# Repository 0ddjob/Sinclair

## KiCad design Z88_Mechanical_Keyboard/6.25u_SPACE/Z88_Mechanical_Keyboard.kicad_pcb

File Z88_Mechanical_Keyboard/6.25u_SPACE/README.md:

# 6.25u SPACE BAR
This PCB design has the 6.25u SPACE and 1.75u CAPS LOCK.

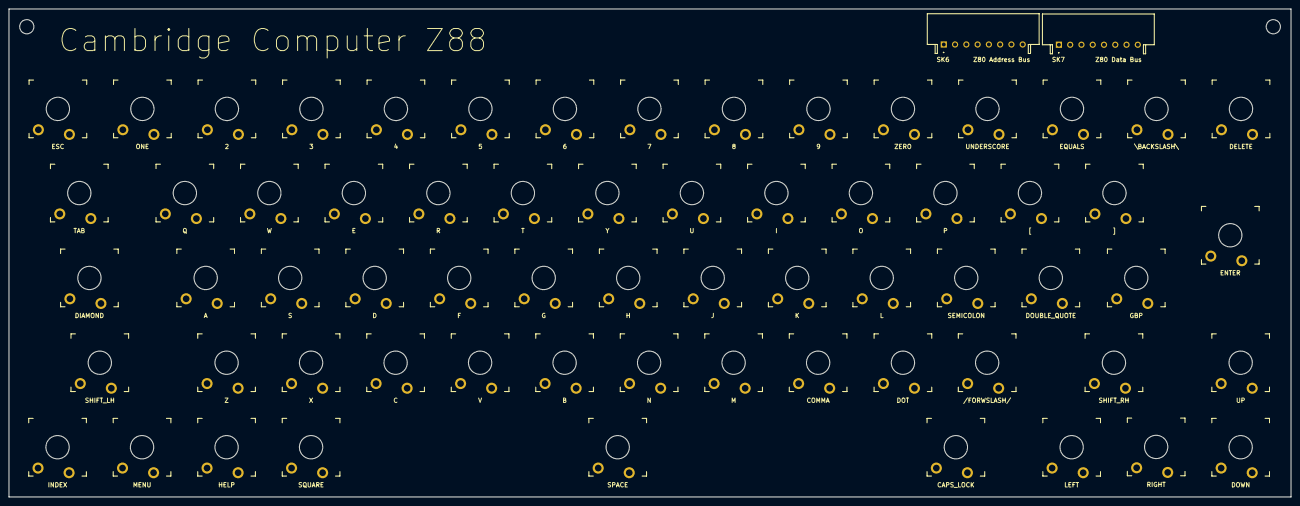
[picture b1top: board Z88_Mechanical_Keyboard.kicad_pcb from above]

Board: 2 copper layers, 289.0 x 110.0 mm, 68 parts (0 on the bottom side), 16 nets, no tracks yet.

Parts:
H1, H2: MountingHole; MountingHole_3.2mm_M3
SK6: Z80 Address Bus; 55203148
SK7: Z80 Data Bus; 55203148
SW1: SHIFT_RH; SW_Gateron_LowProfile_THT
SW2: HELP; SW_Gateron_LowProfile_THT
SW3: [; SW_Gateron_LowProfile_THT
SW4: ]; SW_Gateron_LowProfile_THT
SW5: UNDERSCORE; SW_Gateron_LowProfile_THT
SW6: EQUALS; SW_Gateron_LowProfile_THT
SW7: \BACKSLASH\; SW_Gateron_LowProfile_THT
SW8: DELETE; SW_Gateron_LowProfile_THT
SW9: SQUARE; SW_Gateron_LowProfile_THT
SW10: SHIFT_LH; SW_Gateron_LowProfile_THT
SW11: SPACE; SW_Gateron_LowProfile_THT
SW12: LEFT; SW_Gateron_LowProfile_THT
SW13: RIGHT; SW_Gateron_LowProfile_THT
SW14: DOWN; SW_Gateron_LowProfile_THT
SW15: UP; SW_Gateron_LowProfile_THT
SW16: ENTER; SW_Gateron_LowProfile_THT
SW17: ESC; SW_Gateron_LowProfile_THT
SW18: TAB; SW_Gateron_LowProfile_THT
SW19: ONE; SW_Gateron_LowProfile_THT
SW20: 2; SW_Gateron_LowProfile_THT
SW21: 3; SW_Gateron_LowProfile_THT
SW22: 4; SW_Gateron_LowProfile_THT
SW23: 5; SW_Gateron_LowProfile_THT
SW24: 6; SW_Gateron_LowProfile_THT
SW25: INDEX; SW_Gateron_LowProfile_THT
SW26: DIAMOND; SW_Gateron_LowProfile_THT
SW27: Q; SW_Gateron_LowProfile_THT
SW28: W; SW_Gateron_LowProfile_THT
SW29: E; SW_Gateron_LowProfile_THT
SW30: R; SW_Gateron_LowProfile_THT
SW31: T; SW_Gateron_LowProfile_THT
SW32: Y; SW_Gateron_LowProfile_THT
SW33: CAPS_LOCK; SW_Gateron_LowProfile_THT
SW34: MENU; SW_Gateron_LowProfile_THT
SW35: A; SW_Gateron_LowProfile_THT
SW36: S; SW_Gateron_LowProfile_THT
SW37: D; SW_Gateron_LowProfile_THT
SW38: F; SW_Gateron_LowProfile_THT
SW39: G; SW_Gateron_LowProfile_THT
SW40: H; SW_Gateron_LowProfile_THT
SW41: DOT; SW_Gateron_LowProfile_THT
SW42: COMMA; SW_Gateron_LowProfile_THT
SW43: Z; SW_Gateron_LowProfile_THT
SW44: X; SW_Gateron_LowProfile_THT
SW45: C; SW_Gateron_LowProfile_THT
SW46: V; SW_Gateron_LowProfile_THT
SW47: B; SW_Gateron_LowProfile_THT
SW48: N; SW_Gateron_LowProfile_THT
SW49: /FORWSLASH/; SW_Gateron_LowProfile_THT
SW50: SEMICOLON; SW_Gateron_LowProfile_THT
SW51: L; SW_Gateron_LowProfile_THT
SW52: M; SW_Gateron_LowProfile_THT
SW53: K; SW_Gateron_LowProfile_THT
SW54: J; SW_Gateron_LowProfile_THT
SW55: U; SW_Gateron_LowProfile_THT
SW56: 7; SW_Gateron_LowProfile_THT
SW57: GBP; SW_Gateron_LowProfile_THT
SW58: DOUBLE_QUOTE; SW_Gateron_LowProfile_THT
SW59: ZERO; SW_Gateron_LowProfile_THT
SW60: P; SW_Gateron_LowProfile_THT
SW61: 9; SW_Gateron_LowProfile_THT
SW62: O; SW_Gateron_LowProfile_THT
SW63: I; SW_Gateron_LowProfile_THT
SW64: 8; SW_Gateron_LowProfile_THT

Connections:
COL0: SK6.2, SW1.1, SW9.1, SW17.1, SW25.1, SW33.1, SW41.1, SW49.1, SW57.1
COL1: SK6.1, SW2.1, SW10.1, SW18.1, SW26.1, SW34.1, SW42.1, SW50.1, SW58.1
COL2: SK6.3, SW3.1, SW11.1, SW19.1, SW27.1, SW35.1, SW43.1, SW51.1, SW59.1
COL3: SK6.4, SW4.1, SW12.1, SW20.1, SW28.1, SW36.1, SW44.1, SW52.1, SW60.1
COL4: SK6.5, SW5.1, SW13.1, SW21.1, SW29.1, SW37.1, SW45.1, SW53.1, SW61.1
COL5: SK6.6, SW6.1, SW14.1, SW22.1, SW30.1, SW38.1, SW46.1, SW54.1, SW62.1
COL6: SK6.7, SW7.1, SW15.1, SW23.1, SW31.1, SW39.1, SW47.1, SW55.1, SW63.1
COL7: SK6.8, SW8.1, SW16.1, SW24.1, SW32.1, SW40.1, SW48.1, SW56.1, SW64.1
ROW0: SK7.5, SW1.2, SW2.2, SW3.2, SW4.2, SW5.2, SW6.2, SW7.2, SW8.2
ROW1: SK7.7, SW9.2, SW10.2, SW11.2, SW12.2, SW13.2, SW14.2, SW15.2, SW16.2
ROW2: SK7.1, SW17.2, SW18.2, SW19.2, SW20.2, SW21.2, SW22.2, SW23.2, SW24.2
ROW3: SK7.2, SW25.2, SW26.2, SW27.2, SW28.2, SW29.2, SW30.2, SW31.2, SW32.2
ROW4: SK7.3, SW33.2, SW34.2, SW35.2, SW36.2, SW37.2, SW38.2, SW39.2, SW40.2
ROW5: SK7.8, SW41.2, SW42.2, SW43.2, SW44.2, SW45.2, SW46.2, SW47.2, SW48.2
ROW6: SK7.4, SW49.2, SW50.2, SW51.2, SW52.2, SW53.2, SW54.2, SW55.2, SW56.2
ROW7: SK7.6, SW57.2, SW58.2, SW59.2, SW60.2, SW61.2, SW62.2, SW63.2, SW64.2

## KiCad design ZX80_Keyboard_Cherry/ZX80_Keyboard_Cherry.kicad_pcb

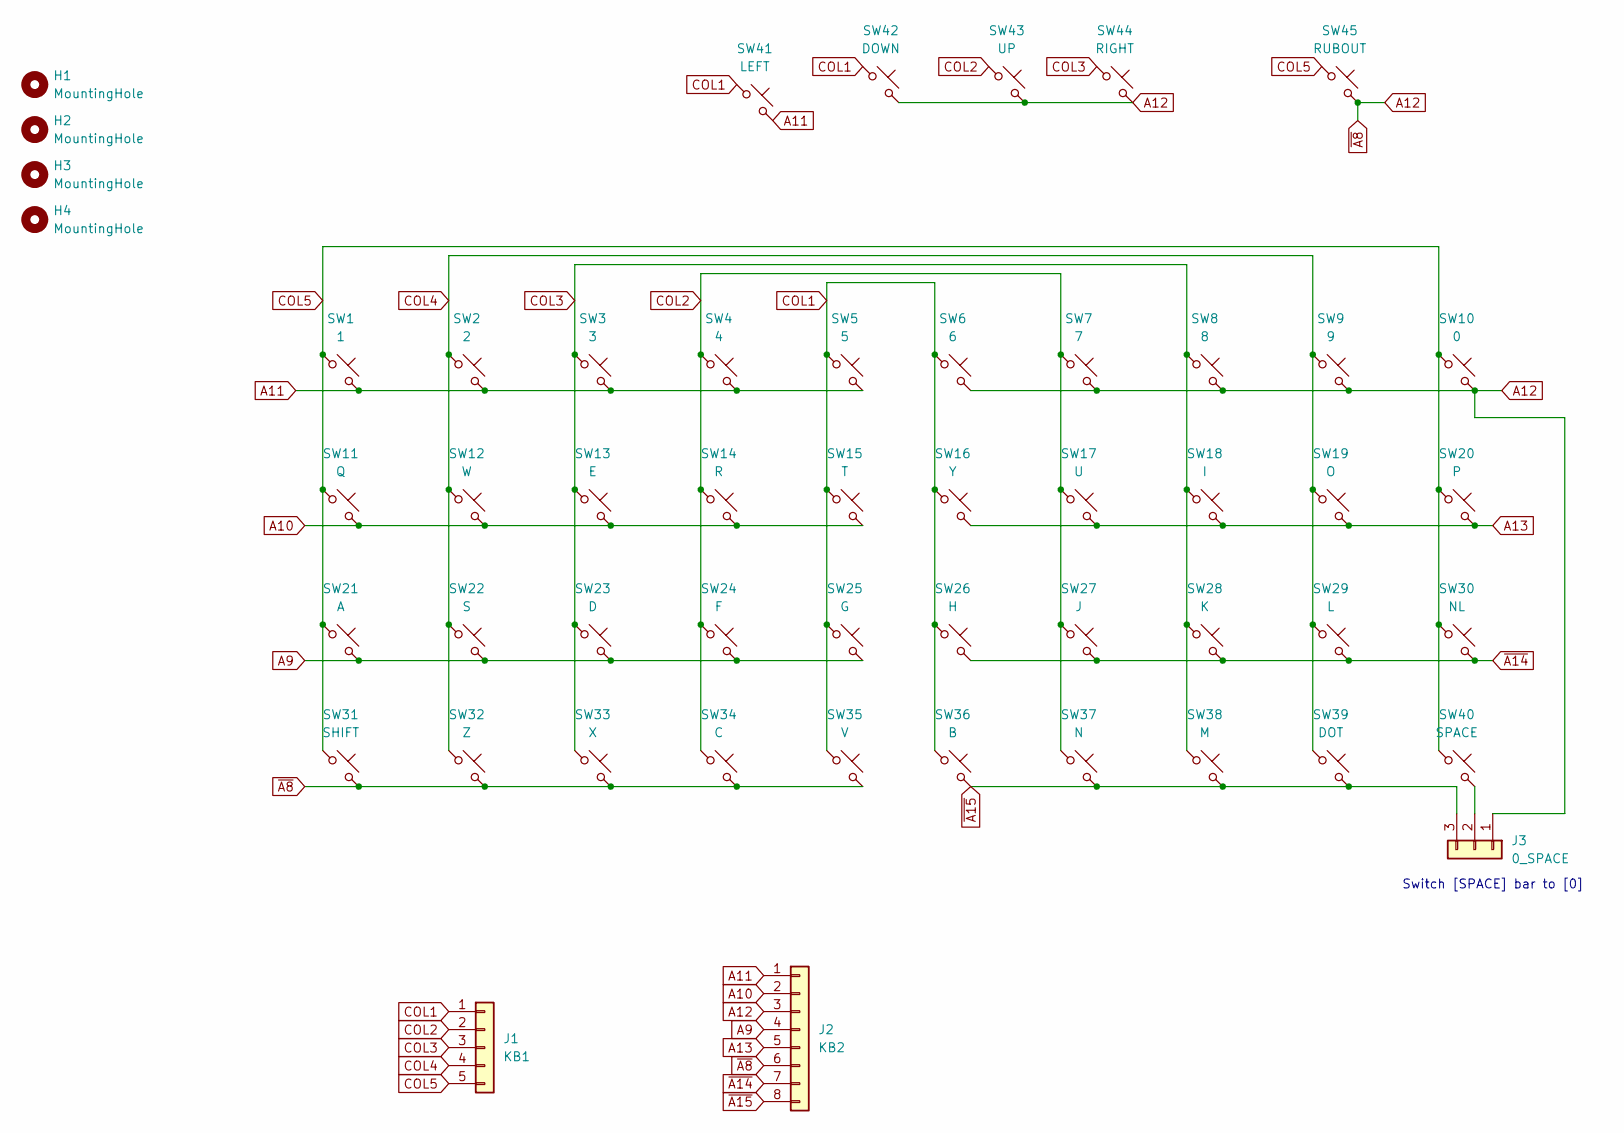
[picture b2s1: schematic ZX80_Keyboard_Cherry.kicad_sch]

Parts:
H1, H2, H3, H4: MountingHole; MountingHole_3.2mm_M3
J1: KB1; PinHeader_1x05_P2.54mm_Vertical
J2: KB2; PinHeader_1x08_P2.54mm_Vertical
J3: 0_SPACE; PinHeader_1x03_P2.54mm_Vertical
SW1: 1; SW_Cherry_MX_1.00u_PCB
SW2: 2; SW_Cherry_MX_1.00u_PCB
SW3: 3; SW_Cherry_MX_1.00u_PCB
SW4: 4; SW_Cherry_MX_1.00u_PCB
SW5: 5; SW_Cherry_MX_1.00u_PCB
SW6: 6; SW_Cherry_MX_1.00u_PCB
SW7: 7; SW_Cherry_MX_1.00u_PCB
SW8: 8; SW_Cherry_MX_1.00u_PCB
SW9: 9; SW_Cherry_MX_1.00u_PCB
SW10: 0; SW_Cherry_MX_1.00u_PCB
SW11: Q; SW_Cherry_MX_1.00u_PCB
SW12: W; SW_Cherry_MX_1.00u_PCB
SW13: E; SW_Cherry_MX_1.00u_PCB
SW14: R; SW_Cherry_MX_1.00u_PCB
SW15: T; SW_Cherry_MX_1.00u_PCB
SW16: Y; SW_Cherry_MX_1.00u_PCB
SW17: U; SW_Cherry_MX_1.00u_PCB
SW18: I; SW_Cherry_MX_1.00u_PCB
SW19: O; SW_Cherry_MX_1.00u_PCB
SW20: P; SW_Cherry_MX_1.00u_PCB
SW21: A; SW_Cherry_MX_1.00u_PCB
SW22: S; SW_Cherry_MX_1.00u_PCB
SW23: D; SW_Cherry_MX_1.00u_PCB
SW24: F; SW_Cherry_MX_1.00u_PCB
SW25: G; SW_Cherry_MX_1.00u_PCB
SW26: H; SW_Cherry_MX_1.00u_PCB
SW27: J; SW_Cherry_MX_1.00u_PCB
SW28: K; SW_Cherry_MX_1.00u_PCB
SW29: L; SW_Cherry_MX_1.00u_PCB
SW30: NL; SW_Cherry_MX_1.00u_PCB
SW31: SHIFT; SW_Cherry_MX_1.00u_PCB
SW32: Z; SW_Cherry_MX_1.00u_PCB
SW33: X; SW_Cherry_MX_1.00u_PCB
SW34: C; SW_Cherry_MX_1.00u_PCB
SW35: V; SW_Cherry_MX_1.00u_PCB
SW36: B; SW_Cherry_MX_1.00u_PCB
SW37: N; SW_Cherry_MX_1.00u_PCB
SW38: M; SW_Cherry_MX_1.00u_PCB
SW39: DOT; SW_Cherry_MX_1.00u_PCB
SW40: SPACE; SW_Cherry_MX_1.00u_PCB
SW41: LEFT; SW_Cherry_MX_1.00u_PCB
SW42: DOWN; SW_Cherry_MX_1.00u_PCB
SW43: UP; SW_Cherry_MX_1.00u_PCB
SW44: RIGHT; SW_Cherry_MX_1.00u_PCB
SW45: RUBOUT; SW_Cherry_MX_1.00u_PCB

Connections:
A9: J2.4, SW21.2, SW22.2, SW23.2, SW24.2, SW25.2
A10: J2.2, SW11.2, SW12.2, SW13.2, SW14.2, SW15.2
A11: J2.1, SW1.2, SW2.2, SW3.2, SW4.2, SW5.2, SW41.2
A12: J2.3, J2.6, J3.1, SW6.2, SW7.2, SW8.2, SW9.2, SW10.2, SW31.2, SW32.2, SW33.2, SW34.2, SW35.2, SW42.2, SW43.2, SW44.2, SW45.2
A13: J2.5, SW16.2, SW17.2, SW18.2, SW19.2, SW20.2
COL1: J1.1, SW5.1, SW6.1, SW15.1, SW16.1, SW25.1, SW26.1, SW35.1, SW36.1, SW41.1, SW42.1
COL2: J1.2, SW4.1, SW7.1, SW14.1, SW17.1, SW24.1, SW27.1, SW34.1, SW37.1, SW43.1
COL3: J1.3, SW3.1, SW8.1, SW13.1, SW18.1, SW23.1, SW28.1, SW33.1, SW38.1, SW44.1
COL4: J1.4, SW2.1, SW9.1, SW12.1, SW19.1, SW22.1, SW29.1, SW32.1, SW39.1
COL5: J1.5, SW1.1, SW10.1, SW11.1, SW20.1, SW21.1, SW30.1, SW31.1, SW40.1, SW45.1
unnamed: J3.2, SW40.2
~A14: J2.7, SW26.2, SW27.2, SW28.2, SW29.2, SW30.2
~A15: J2.8, J3.3, SW36.2, SW37.2, SW38.2, SW39.2

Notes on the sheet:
Switch [SPACE] bar to [0]

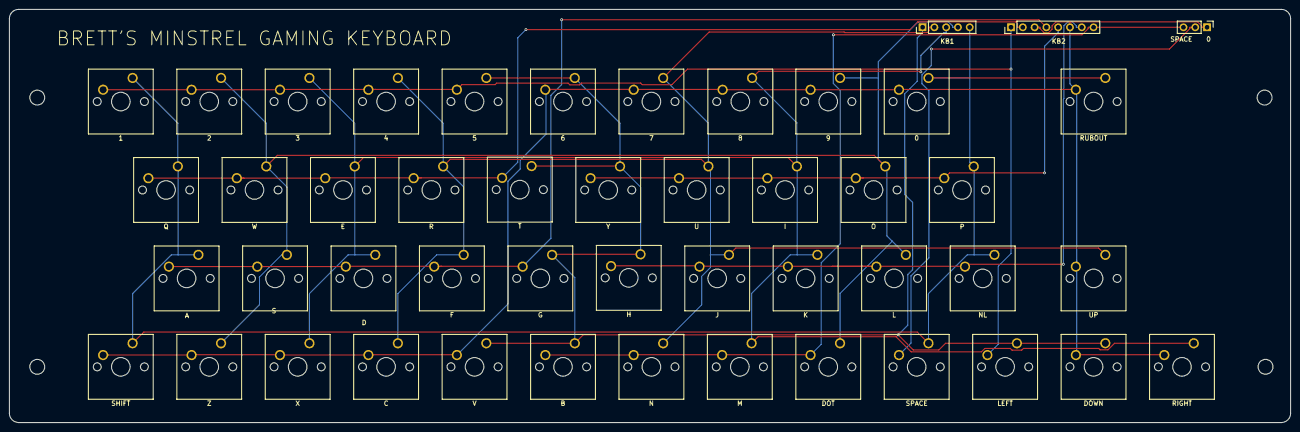
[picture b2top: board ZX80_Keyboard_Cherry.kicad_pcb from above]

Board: 2 copper layers, 276.0 x 89.0 mm, 52 parts (0 on the bottom side), 13 nets.

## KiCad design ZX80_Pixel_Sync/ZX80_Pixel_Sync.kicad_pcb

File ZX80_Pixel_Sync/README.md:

# ZX80 Pixel Synchronisation
This daughterboard for the Minstrel 2 v2.8 or earlier fixes an issue in the original ZX80's video output circuit.<br>

The issue would not have been noticeable back in the 1980s if using a CRT.<br>

The fix was created by Dave at Tynemouth Software for his Minstrel 2 computer, a recreation of the ZX80.  This fix is already implemented in the v2.9 board (latest as at May-2025).<br>

## Background
Please refer to Dave's blog posts where he details the issue and how he fixed it.<br>
- [Minstrel 2 Pixel Synchronisation (Part 1)](http://blog.tynemouthsoftware.co.uk/2022/09/minstrel-2-pixel-synchronisation-part-1.html)
- [Minstrel 2 Pixel Synchronisation (Part 2)](http://blog.tynemouthsoftware.co.uk/2022/09/minstrel-2-pixel-synchronisation-part-2.html)

## My Implementation
Thanks to Dave's help supplying me with the v2.6 and v2.9 schematics I was able to design a daughterboard that can replace the 74LS08 on the pre-V2.9 boards that replicates his fix.<br>

This has been successfully tested (Rev. A).  I didn't like how the tap wires crossed over each other so I re-arranged them and created a Rev. B board - this has not yet been tested but, apart from the re-arranged tap signals, is idential to Rev. A.<br>

## Testing
This YouTube video covers the testing of this board:<br>
[Minstrel 2 (Sinclair ZX80 Clone): Part 2 (Pixel Synch. Issue)](https://youtu.be/O-Urgigq2Vk)

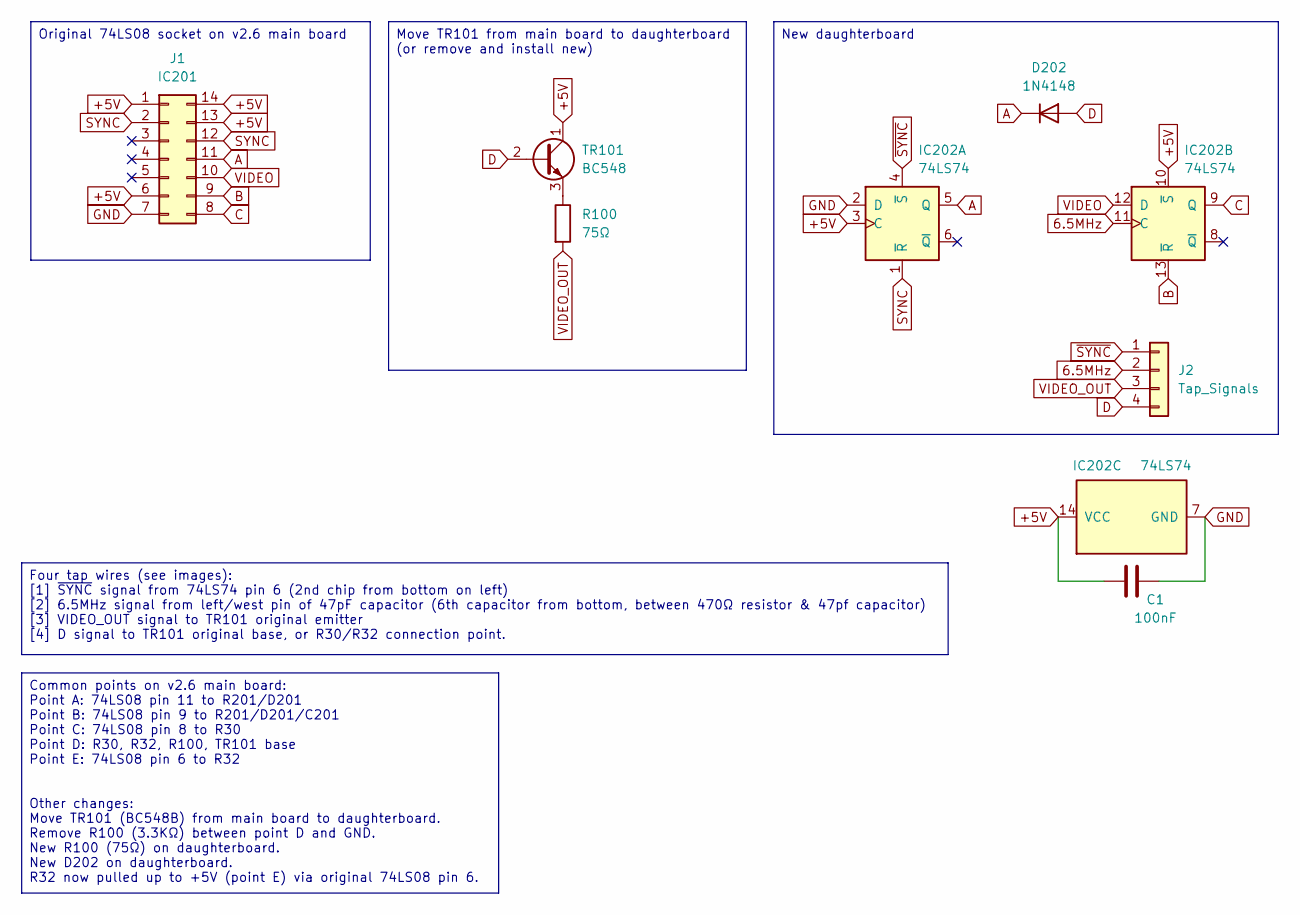
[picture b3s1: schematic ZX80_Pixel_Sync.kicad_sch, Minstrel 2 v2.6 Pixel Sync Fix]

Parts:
C1: 100nF; C_Disc_D3.0mm_W2.0mm_P2.50mm
D202: 1N4148; D_DO-35_SOD27_P7.62mm_Horizontal
IC202: 74LS74; DIP-14_W7.62mm
J1: IC201; DIP-14_W7.62mm_Socket
J2: Tap_Signals; PinHeader_1x04_P2.54mm_Vertical
R100: 75Ω; R_Axial_DIN0207_L6.3mm_D2.5mm_P7.62mm_Horizontal
TR101: BC548; TO-92_Inline

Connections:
6.5MHz: IC202.11 (C), J2.2
+5V: C1.2, IC202.3 (C), IC202.10 (~S), IC202.14 (VCC), J1.1, J1.6, J1.13, J1.14, TR101.1 (C)
A: D202.1 (K), IC202.5 (Q), J1.11
B: IC202.13 (~R), J1.9
C: IC202.9 (Q), J1.8
D: D202.2 (A), J2.4, TR101.2 (B)
GND: C1.1, IC202.2 (D), IC202.7 (GND), J1.7
unnamed: R100.1, TR101.3 (E)
SYNC: IC202.1 (~R), J1.2, J1.12
VIDEO: IC202.12 (D), J1.10
VIDEO_OUT: J2.3, R100.2
~SYNC: IC202.4 (~S), J2.1

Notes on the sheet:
Original 74LS08 socket on v2.6 main board
Common points on v2.6 main board: Point A: 74LS08 pin 11 to R201/D201 Point B: 74LS08 pin 9 to R201/D201/C201 Point C: 74LS08 pin 8 to R30 Point D: R30, R32, R100, TR101 base Point E: 74LS08 pin 6 to R32 Other changes: Move TR101 (BC548B) from main board to daughterboard. Remove R100 (3.3KΩ) betwee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
Move TR101 from main board to daughterboard (or remove and install new)
New daughterboard
Four tap wires (see images): [1] ~{SYNC} signal from 74LS74 pin 6 (2nd chip from bottom on left) [2] 6.5MHz signal from left/west pin of 47pF capacitor (6th capacitor from bottom, between 470Ω resistor & 47pf capacitor) [3] VIDEO_OUT signal to TR101 original emitter [4] D signal to TR101 original b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

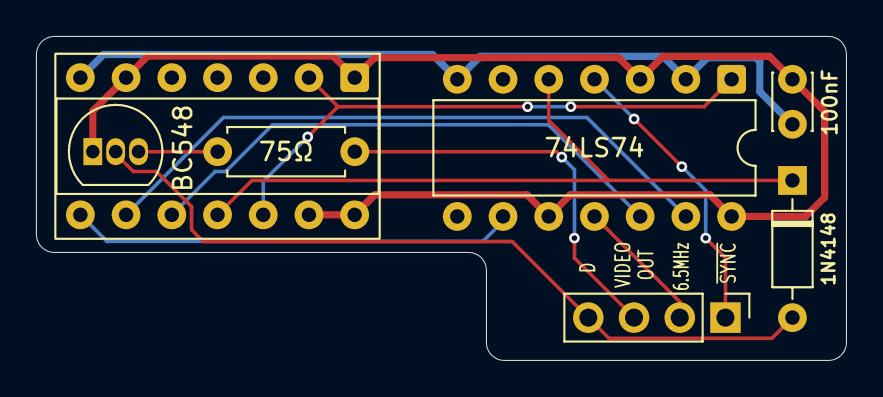
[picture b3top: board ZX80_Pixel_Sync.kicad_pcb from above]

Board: 2 copper layers, 45.0 x 18.0 mm, 7 parts (0 on the bottom side), 12 nets.

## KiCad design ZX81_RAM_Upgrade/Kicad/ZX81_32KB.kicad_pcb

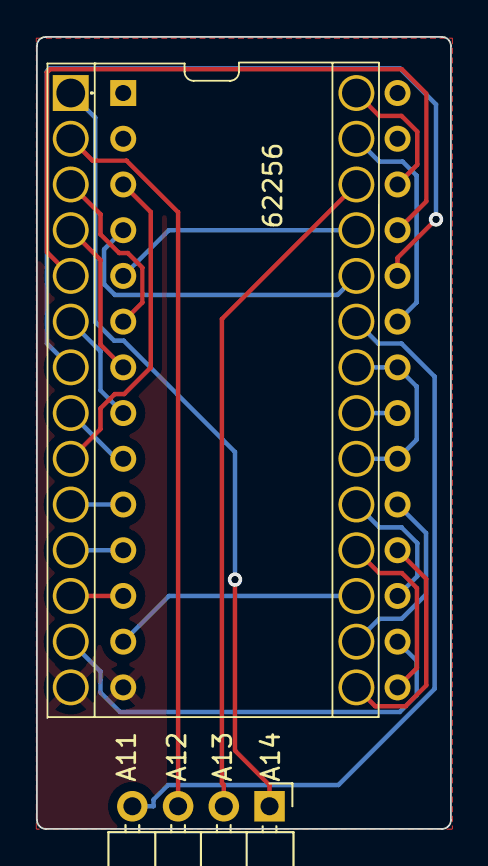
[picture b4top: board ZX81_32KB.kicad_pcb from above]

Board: 2 copper layers, 23.0 x 44.0 mm, 3 parts (0 on the bottom side), 27 nets.

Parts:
IC1: CY62256NLL-55SNXI; DIP1587W140P254L3632H381Q28N
J3: Conn_01x04_Pin; PinHeader_1x04_P2.54mm_Horizontal
J4: 828-AG11D-LF; 828AG11DLF

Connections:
/+5V: IC1.28 (VCC), J4.26
/A00: IC1.10 (A0), J4.10
/A01: IC1.9 (A1), J4.3
/A02: IC1.8 (A2), J4.9
/A03: IC1.7 (A3), J4.24
/A04: IC1.6 (A4), J4.8
/A05: IC1.5 (A5), J4.25
/A06: IC1.4 (A6), J4.7
/A07: IC1.3 (A7), J4.6
/A08: IC1.25 (A8), J4.5
/A09: IC1.24 (A9), J4.4
/A10: IC1.21 (A10), J4.21
/A11: IC1.23 (A11), J3.4
/A12: IC1.2 (A12), J3.3
/A13: IC1.26 (A13), J3.2
/A14: IC1.1 (A14), J3.1
/D0: IC1.11 (DQ0), J4.11
/D1: IC1.12 (DQ1), J4.12
/D2: IC1.13 (DQ2), J4.16
/D3: IC1.15 (DQ3), J4.18
/D4: IC1.16 (DQ4), J4.19
/D5: IC1.17 (DQ5), J4.13
/D6: IC1.18 (DQ6), J4.15
/D7: IC1.19 (DQ7), J4.17
/GND: IC1.14 (VSS), J4.14
/~RAMCS: IC1.20 (CE#), IC1.22 (OE#), J4.20, J4.22
/~WR: IC1.27 (WE#), J4.23
